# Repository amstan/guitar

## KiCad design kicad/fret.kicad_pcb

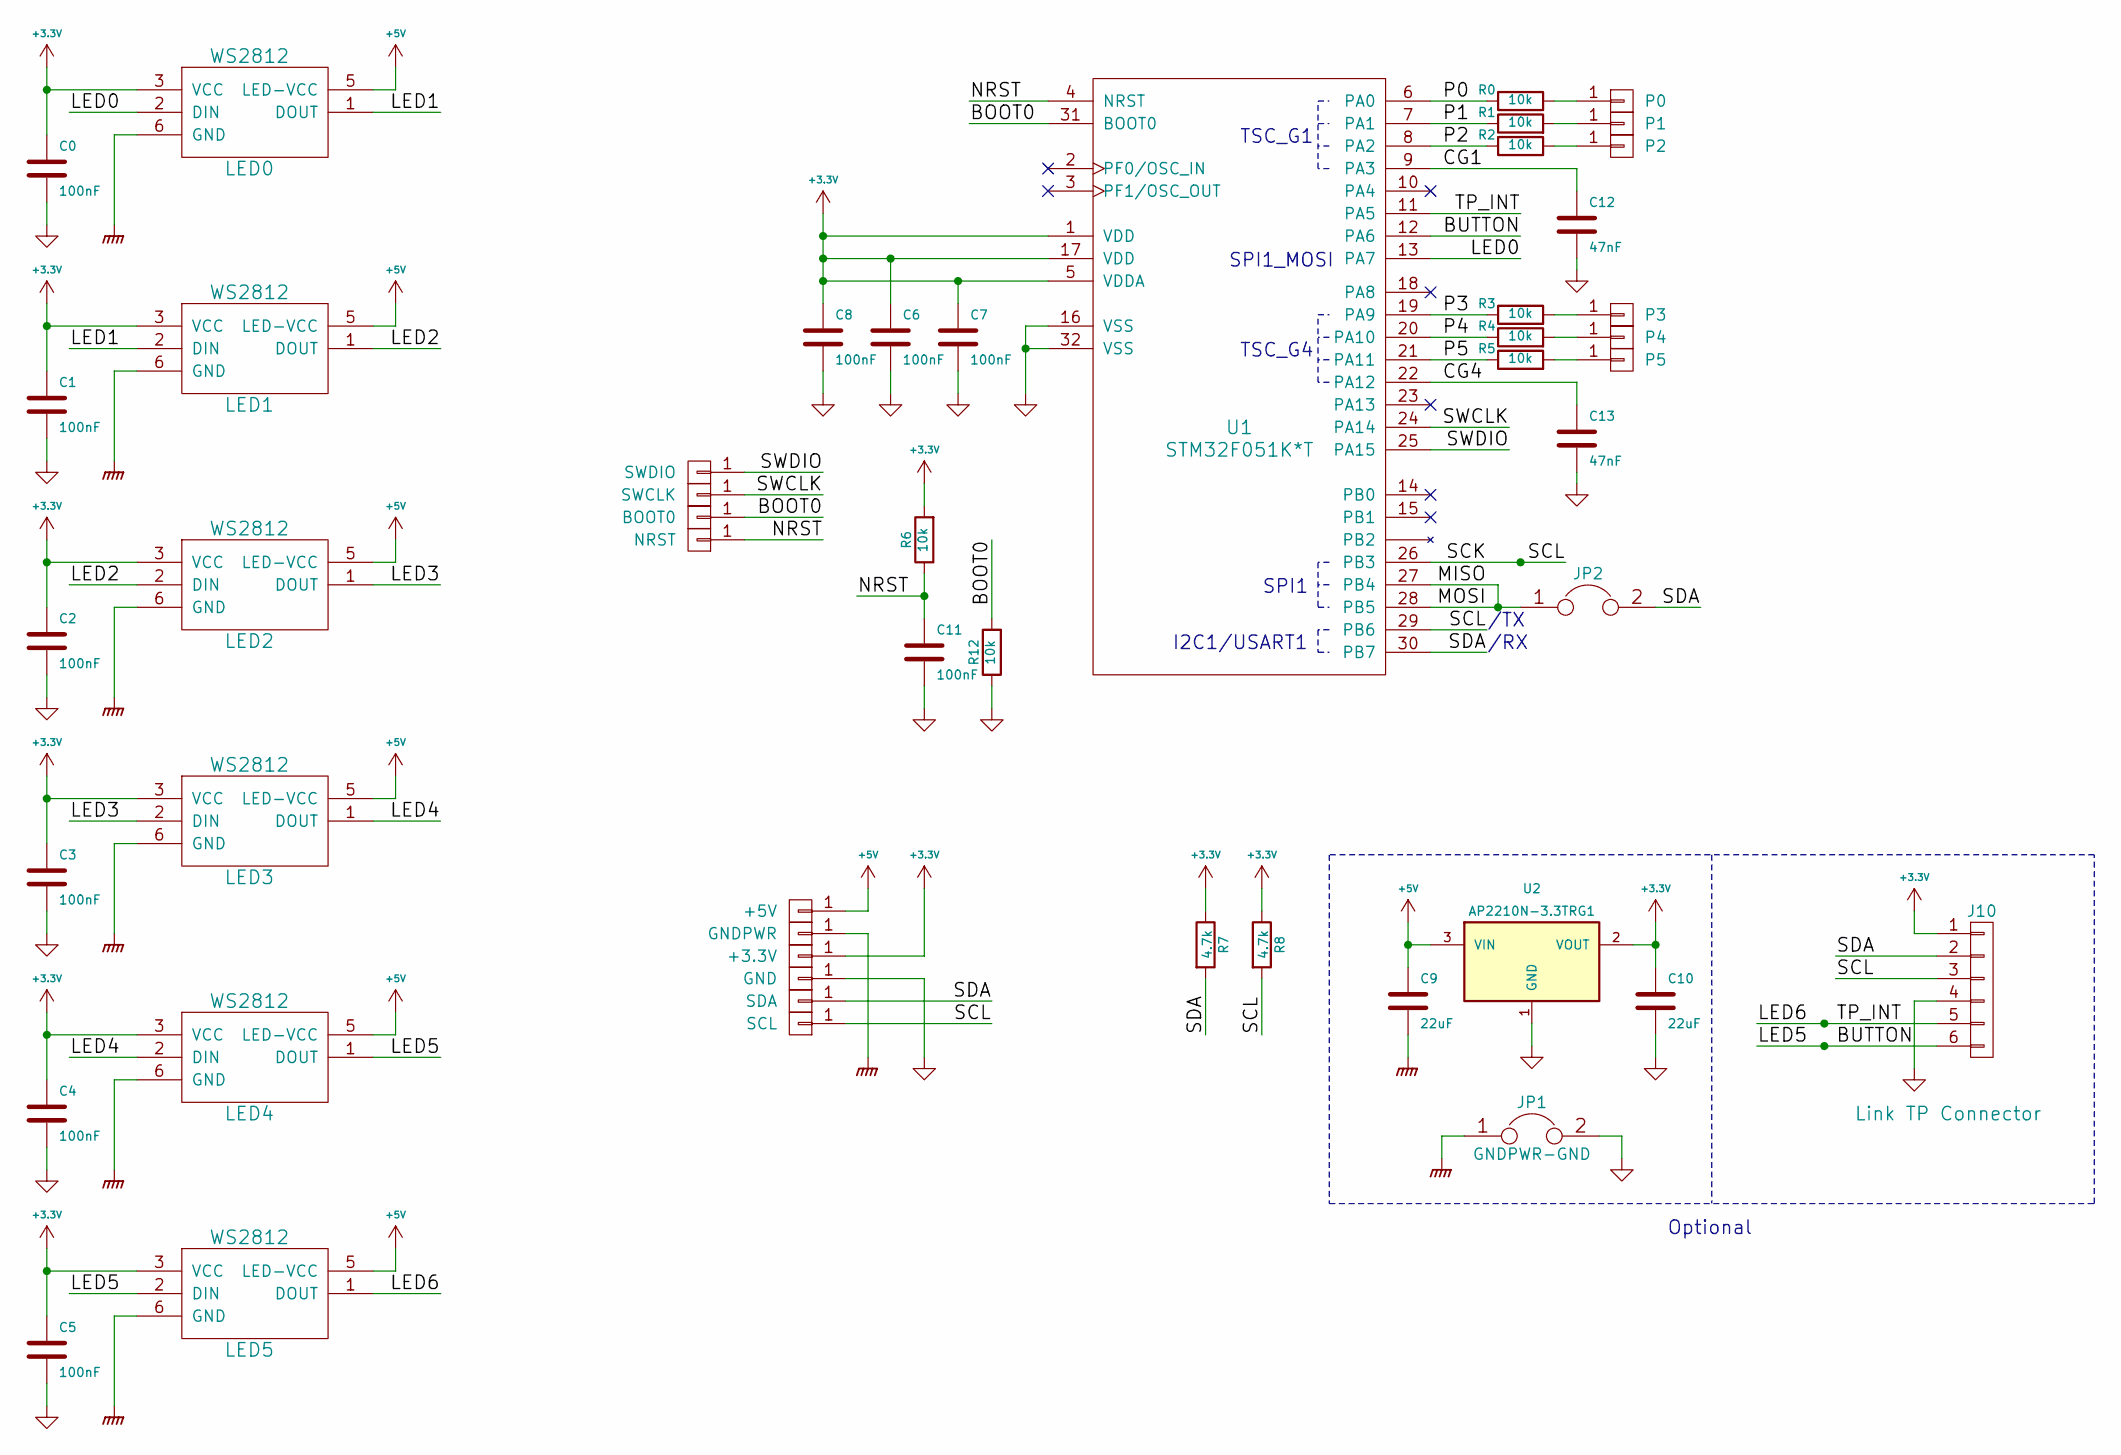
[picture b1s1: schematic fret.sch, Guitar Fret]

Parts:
C0, C1, C2, C3, C4, C5, C6, C7, C8, C11: 100nF; C_0603; Digi-Key Page 100nF
C9, C10: 22uF; C_0805; Digi-Key Page 22nF
C12, C13: 47nF; C_0603; Digi-Key Page 47nF
J1: +5V; IDC-1x1
J2: GNDPWR; IDC-1x1
J3: +3.3V; IDC-1x1
J4: GND; IDC-1x1
J5: SDA; IDC-1x1
J6: SCL; IDC-1x1
J7: BOOT0; pad-2mm-round; Digi-Key Page n/a
J8: NRST; pad-2mm-round; Digi-Key Page n/a
J9: SWDIO; pad-2mm-round; Digi-Key Page n/a
J10: CONN_01X06; Connector_Molex_PicoBlade_53261-0471; Digi-Key Page todo
J11: SWCLK; pad-2mm-round; Digi-Key Page n/a
JP1: GNDPWR-GND; R_0603; Digi-Key Page 0ohm
JP2: SPI-CONNECTION; R_0603; Digi-Key Page 0ohm
LED0, LED1, LED2, LED3, LED4, LED5: WS2812; 5050-6pin
P0, P1, P2, P3, P4, P5: TOUCH; TP-8x15; Digi-Key Page n/a
R0, R1, R2, R3, R4, R5, R6, R12: 10k; R_0603; Digi-Key Page 10k
R7, R8: 4.7k; R_0603; Digi-Key Page 4.7k
U1: STM32F051K*T; LQFP-32_7x7mm_Pitch0.8mm
U2: AP2210N-3.3TRG1; SOT-23

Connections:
+3V3: C0.1, C1.1, C2.1, C3.1, C4.1, C5.1, C6.1, C7.1, C8.1, C10.1, J3.1, J10.1, LED0.3 (VCC), LED1.3 (VCC), LED2.3 (VCC), LED3.3 (VCC), LED4.3 (VCC), LED5.3 (VCC), R6.2, R7.1, R8.1, U1.1 (VDD), U1.5 (VDDA), U1.17 (VDD), U2.2 (VOUT)
+5V: C9.1, J1.1, LED0.5 (LED-VCC), LED1.5 (LED-VCC), LED2.5 (LED-VCC), LED3.5 (LED-VCC), LED4.5 (LED-VCC), LED5.5 (LED-VCC), U2.3 (VIN)
/BOOT0: J7.1, R12.2, U1.31 (BOOT0)
/BUTTON: J10.6, LED4.1 (DOUT), LED5.2 (DIN), U1.12 (PA6)
/CG1: C12.1, U1.9 (PA3)
/CG4: C13.1, U1.22 (PA12)
/LED0: LED0.2 (DIN), U1.13 (PA7)
/LED1: LED0.1 (DOUT), LED1.2 (DIN)
/LED2: LED1.1 (DOUT), LED2.2 (DIN)
/LED3: LED2.1 (DOUT), LED3.2 (DIN)
/LED4: LED3.1 (DOUT), LED4.2 (DIN)
/LED6: J10.5, LED5.1 (DOUT), U1.11 (PA5)
/MISO: JP2.1, U1.27 (PB4), U1.28 (PB5)
/NRST: C11.1, J8.1, R6.1, U1.4 (NRST)
/P0: R0.1, U1.6 (PA0)
/P1: R1.1, U1.7 (PA1)
/P2: R2.1, U1.8 (PA2)
/P3: R3.1, U1.19 (PA9)
/P4: R4.1, U1.20 (PA10)
/P5: R5.1, U1.21 (PA11)
/SCK: J6.1, J10.3, R8.2, U1.26 (PB3), U1.29 (PB6)
/SDA: J5.1, J10.2, JP2.2, R7.2, U1.30 (PB7)
/SWCLK: J11.1, U1.24 (PA14)
/SWDIO: J9.1, U1.25 (PA15)
GND: C0.2, C1.2, C2.2, C3.2, C4.2, C5.2, C6.2, C7.2, C8.2, C10.2, C11.2, C12.2, C13.2, J4.1, J10.4, JP1.2, R12.1, U1.16 (VSS), U1.32 (VSS), U2.1 (GND)
GNDPWR: C9.2, J2.1, JP1.1, LED0.6 (GND), LED1.6 (GND), LED2.6 (GND), LED3.6 (GND), LED4.6 (GND), LED5.6 (GND)
unnamed: P0.1, R0.2
unnamed: P1.1, R1.2
unnamed: P2.1, R2.2
unnamed: P3.1, R3.2
unnamed: P4.1, R4.2
unnamed: P5.1, R5.2

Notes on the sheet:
Optional
SPI1
I2C1/USART1
/RX
/TX
SPI1_MOSI
TSC_G1
TSC_G4

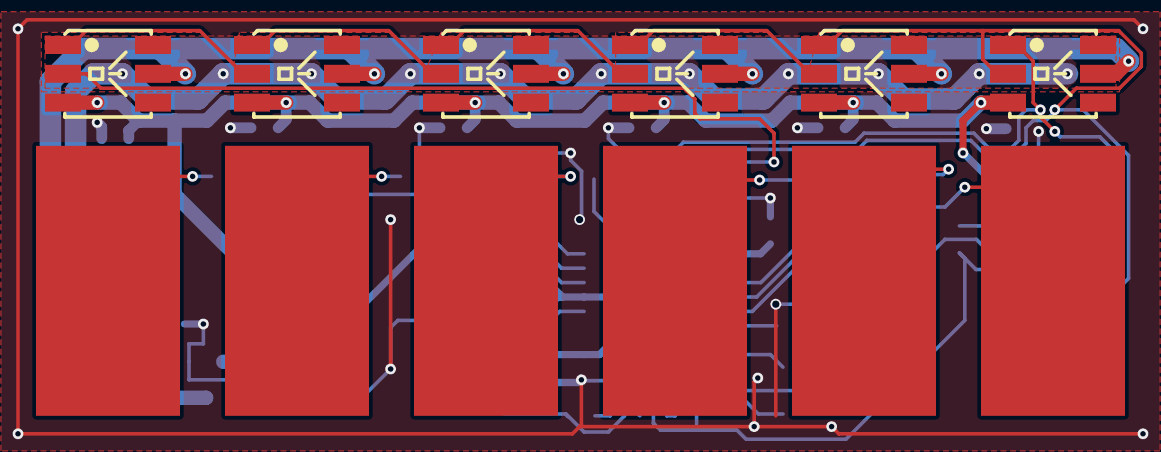
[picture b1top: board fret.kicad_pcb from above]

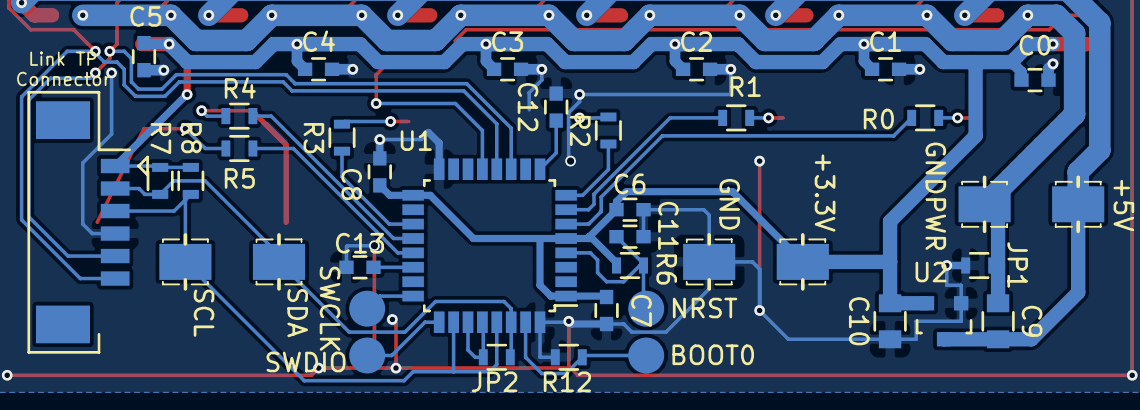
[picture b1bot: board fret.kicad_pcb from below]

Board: 2 copper layers, 51 parts (39 on the bottom side), 32 nets.

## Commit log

2010-01-11 initial comit
2010-01-11 working makefile
2010-01-11 deleted random jack file
2010-01-12 fixed emulator crash when pressing volume keys
2010-01-12 fixed changed but not updated git thingy
2010-01-12 args library done
2010-01-12 jack stuff all moved to jack.c, main is not jack free
2010-01-12 main.c: load_notes free of magic numbers
2010-01-14 moved notes, added prototypes
2010-01-14 added prototypes to jack, renamed notes functions, initialization checking added
2010-01-14 added doxygen
2010-01-14 added some files
2010-01-14 moved tuning to separate file
2010-01-14 moved more stuff to their files + renaming
2010-01-15 configuration library added, all playable too
2010-01-16 chord mappings now detects when a string ends, and format updated to include fret numbers
2010-01-18 added transposing
2010-01-18 changed config file organization
2010-01-18 make sure multiple instances can run at the same time
2010-01-18 added port autoconnection
2010-01-18 updated doc, added support for lots of docs
2010-01-18 undebuged chords.c
2010-01-20 notes_translate, organized etc
2010-01-20 notes_translate is now used in places
2010-01-20 fixed misc stuff in main.c
2010-02-20 moved code in a folder
2010-02-20 added electronics
2010-02-21 working touch switch
2010-02-21 changed the touchswitch to use pnp darlington and now i get 4.3V-0.027V
2010-02-21 implemented the new darlington in the schematic
2010-02-21 fixed touchpad jumper to supply gnd instead of vcc
2010-02-21 added option buttons, finished eagle sch
2010-02-23 added missing caps for touchsensor, fixed unconnected wires, started layout of the pcb
2010-02-23 finished layout
2010-02-23 tried autoroute
2010-02-23 started manual routing, changed string capacitors to 1206
2010-02-23 some more touches to pcb traces
2010-02-23 added mcucode, copied from led project
2010-02-23 started doxygen mcucode
2010-02-23 fixed makefile permissions
2010-02-23 copied doxyfile from guitarseq
2010-02-23 fixed some comments in mcucode libaries
2010-02-27 deleted old library file
2010-02-27 fixed documentation
2010-02-27 deleted the compiled docs
2010-02-27 cleaned projects
2010-02-27 got a mainpage.dox for mcucode
2010-02-27 added bit operations library
2010-02-27 cleaned main(old on in raw), added toggle bit, cleaned bitop code
2010-02-27 changed wire names
2010-02-27 configured ports
2010-02-27 started working on the mail loop in mcucode
2010-03-03 added some more pcb wires
2010-03-24 added license file, preparing dbus, preparing more chords
2010-03-25 added more chords and added missing chord error
2010-03-25 completed chords, added standard mappings, extended fifth string in the emulator to 12 frets
2010-03-28 tried some more dbus stuff
2010-05-13 some changes that makes it more suitable for playing
2010-05-13 generated dimensions, neck length: ~55cm
2010-05-16 designed the body
2010-05-16 stylized
2010-05-18 Added side views
2010-05-19 ready for printing v1 body
2010-05-22 Populated the neck with the buttons
2010-05-29 more changes to the body
2010-06-02 changed the StringLEDs to be directly connected to the MCU, changed all the R/C to 805
2010-06-02 moved components around, redid the string touchpad side
2010-06-04 Did most of the PCB Routing
2010-06-13 Made the pcb smaller
2010-06-13 reconnected stuff
2011-06-26 added some uncommited changes from i have no idea when
2011-12-15 moved ldflags to the end, apparently gcc only works that way now
2011-12-15 apparently newjack is eager to start the process before i initialize the ringbuffer. Thanks rwest for the tip.
2013-01-28 random program that recieves the power line hum on a highz pad, counts 60 of them, then prints an * every second based on that
2013-07-18 working,high resolution touch reading from capacitive booster pack
2013-07-18 tried to get the ws2811 going but linker complains
2013-07-18 working rgb led
2013-07-23 Started worrying about the body construction again
2014-12-15 Initial guitarseq stuff
    It uses autogenerated ctypes bindings to talk to jack.
    It also has support for the fast code to be written in C (libguitarseq)
2014-12-15 Started work on schematics
2014-12-15 guitarseq: working note method
2014-12-17 guitarseq: Working barebones with keyboard
2014-12-17 Added callback support, input port
2014-12-19 Working get_ports, thanks dash
2014-12-21 Tried to generate bindings with cffi
    cffi doesn't just parse include files directly,
    stuff like __attribute packed fails miserably unless given as a separate cdef.
2014-12-21 Done switching to a modded jackclient-python
    Helpfully upstream will accept my jackclient changes.
    Everything works except ringbuffers, those are still missing from
    jackclient-python, so a ton of stuff is commented for now.
2014-12-21 Fixed python3 stuff for touchtest
2014-12-21 Everything works perfectly as before (when it was ctypes)
    Yet everything is so much cleaner!
2015-01-17 Update to the new midi port type
2015-01-17 Moved the import notes
2015-01-17 Deprecate python2
2015-01-17 fix a fret release mute string behavoir
2015-01-17 Updated jackclient dependency
    Updated the callback capturing to conform with the new API
2015-01-17 autoconnect
2015-01-18 Stop segfaults under pypy, seems that memory management is just slightly different
2015-01-18 Make info and error prints a little better
2015-01-18 note name printing was broken
2015-01-18 got rid of the CALLBACK_ARG define, a simple cast suffices
2015-01-19 Started work on QGuitarSeq
2015-02-01 added leds
2015-02-02 started looking at stm32f4
2015-02-02 Working usb printf and timer!
2015-02-02 Added sample usb driver from libopencm3
2015-05-20 Making code more compatible with upstream jackclient
    Removed the logging functions from process.c
    Those functions are fugly anyway :) printf is much cleaner.
    error and info also can't be instance methods either (since they belong to the
    whole of jack, not just one client). Made them @staticmethods, even though
    set_*_function eats the callback, it might change in the future.
    The process callback setting was also changed to use the cffi api directly.
2015-05-20 Implemented touchpad on the stm32, wrote python driver to talk to it.
    Driver help from:
    * http://lxr.free-electrons.com/source/drivers/input/touchscreen/atmel_mxt_ts.c
    * https://github.com/SmokyBob/android_kernel_samsung_u8500/blob/master/drivers/input/touchscreen/atmel_mxt224E_cfg.c
2015-05-20 QGuitarSeq
2015-05-20 Hooked up the driver into QGuitarSeq
2015-05-25 Fix flaky enumeration
2015-05-26 trying raw bulk
2015-05-27 2 cdc ports
2015-05-27 renamed endpoints
2015-05-30 stuff not working for some reason
2015-05-31 kicad: Some more work on the fret schematics
2015-05-31 kicad: Renamed components library
2015-05-31 kicad: Annotated components
2015-05-31 kicad: Added netlist
2015-05-31 kicad: renamed guitar to fret
2015-05-31 kicad: Started layout
2015-06-21 kicad: almost finished layout with the msp430
2015-06-21 kicad: switched fret chip, updated pdfs
2015-06-22 kicad: finished stm32 schematics
2015-06-22 kicad: started fret layout with stm32
2015-10-24 kicad: layout was almost finished a while ago
2015-10-24 firmware: reorganize folders
2015-10-25 firmware-fret: f072 discovery board blinks
2015-10-25 removed extra softlinks
2015-10-25 firmware-fret: working touch sensor
2016-02-20 firmware-fret: tried to get i2c-master working with some sample code
2016-02-20 Revert "firmware-fret: tried to get i2c-master working with some sample code"
    This reverts commit 3976860ca7319e98e007d0c3004bc5db1e932244.
2016-02-20 firmware-fret: remove touchpad stuff for now
2016-02-20 firmware-fret: Added version metadata in the binary
2016-02-20 firmware-fret: working i2c-slave framework
2016-02-21 firmware-fret: now we have i2c registers
2016-02-21 firmware-fret: ws2812 driving
    * Bitbanged/fragile ws2812 driver
    * Hooked up to the register
    * Python tester to make pretty colors
2016-02-22 firmware-fret: added touch back in, part of the register map now
2016-02-22 kicad: Ordered fret board
    Board modifications:
    * SWDIO now in the right spot
    * Silkscreen adjustments
    * Testing touchpad silkscreen edge effects on the backend
    Board is v2.0
    Sent order to elecrow.
2016-03-02 fret: fret board v2 is alive!
2016-03-04 fret: fret v2 touch working properly now
2016-03-24 rainbow on the circle
2016-03-24 get rid of annoyingness
2016-03-24 fret: change i2c to be command based
2016-05-11 more stuff
2016-06-04 Some work in openscad
2016-06-04 Reworking stuff in blender
2016-06-06 printed some single ones
2016-12-19 fret: various bug fixes
2017-01-18 fret: fade out
2017-01-20 fret-tester: ec protocol
2017-01-30 ectool: added i2c version 3 protocol
2017-01-30 f0: i2c: fix slave
2017-01-30 Revert "Remove Makefile symlinks under board directory"
    This reverts commit 815b1356903306c66b3a433f0daa4577e1182a2e.
2017-01-30 discovery-stm32f072: simplified board
    * Also switched default uart to UART1, PA9/PA10
2017-01-30 discovery-stm32f072: added i2c slave
2017-01-30 lightbar: rewrite to support ws2812
2017-01-30 lightbar: added EC_CMD_LIGHTBAR_RAW_CMD to burst all leds in one command
2017-01-30 fret: Add support for the new board
2017-01-30 captouch_stm32: add support for the peripheral
2017-01-30 python: Added a python driver for the frets
2017-01-30 python: Fret Collection implementing enumeration of multiple devices
2017-01-30 i2c: auto address support
2017-01-30 working change split size
2017-02-10 python: Implemented touch command
2017-02-10 python: stagger more efficiently
2017-02-10 python: test with all of them
2017-02-10 python: add reboot
2017-02-10 captouch: new task
2017-02-10 flashing all of them
2017-02-10 python: figured out addresses
2017-02-10 lightbar: Make init colors all leds on
2017-02-10 python: fps counting
2017-02-10 python: move tests to function
2017-02-10 python: fade
2017-02-10 python: threaded is so much faster!
2017-02-10 python: sort the frets
2017-02-14 python: rpyc
2017-02-14 force lid on
2017-02-14 better gru leds
2017-02-27 moved: fret-tester out of this repo
2017-02-27 guitarseq: rpyc
2017-03-17 fixup: python: collection
2017-03-17 captouch: better, long history
2017-03-17 touch+leds: demo mode before raw command
2017-05-04 guitarseq: hooked it up to local i2c
2017-05-14 guitarseq: fixed reading in process()
2017-05-14 blender: Preparing to start modifying for the modifier
2017-05-14 blender: Duplicated 10x, applied modifier and filled faces
2017-05-14 blender: 10x ready
2017-05-14 blender: Finished version with screw holes
2017-05-14 blender: worked on head
2017-05-14 body: upgrade body.svg to new inkscape
2017-05-14 body: layout of the components
2017-05-15 body: found dimensions for top ports
2017-05-15 body: just about trying the main baseboard
2017-05-17 body: finished wifisupport baseplate
2017-05-17 body: done???
2017-09-04 body: Finished mk1 for makerfaire
2017-09-04 guitarseq: Added touchpad
    Also removed a bunch of stuff that wasn't needed
    since it's now a local device.
2017-09-04 Added option frets and Touchpad driver
2017-09-04 firmware: removed old firmware folders
    In preparation of the ec submodule
2017-09-04 firmware: imported ec code
2017-09-04 Reorganized/Added python thirdparty libraries
2017-09-04 guitarseq: fix case if the message is for the future
2017-09-11 touchpad: fix y coordinate
2017-09-11 fret: make i2c go faster
2022-06-05 Commit leftover programming stuff
    This has been lying in here for years uncommited.
    Looks like it's something to fixup the programming of the frets.
2022-06-05 Commit uncommited stuff
    These files have been lying around uncommited for years.
    It's exactly what the v2 has been happily running with, so I don't want to touch them when organizing.
